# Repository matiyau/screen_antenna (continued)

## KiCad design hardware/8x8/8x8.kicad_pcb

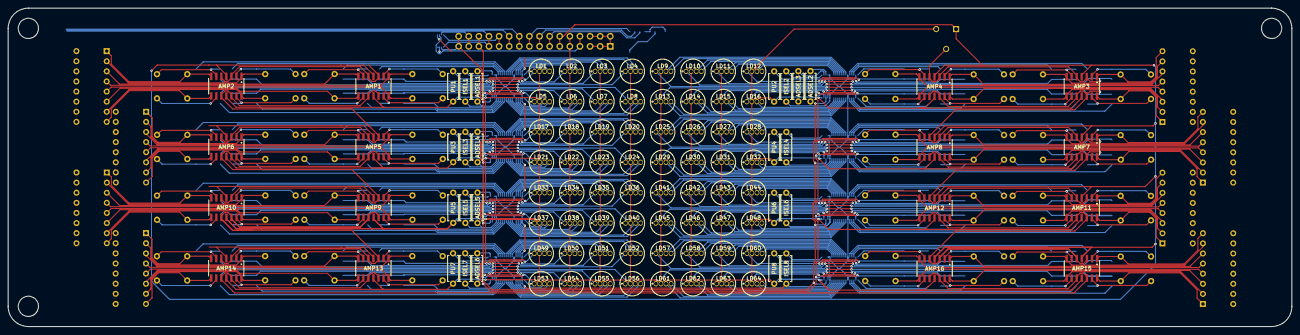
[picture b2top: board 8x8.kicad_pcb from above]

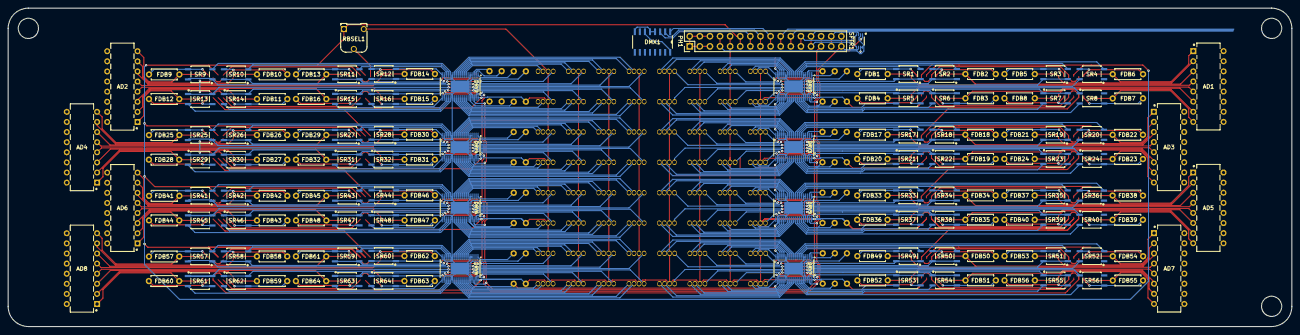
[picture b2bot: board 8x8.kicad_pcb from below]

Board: 2 copper layers, 322.6 x 80.0 mm, 250 parts (148 on the bottom side), 429 nets.

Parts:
AD1, AD2, AD3, AD4, AD5, AD6, AD7, AD8: MCP3008-I/P-DIP16; MCP3008-I&slash_P
ADSEL1, ADSEL2, ADSEL3, ADSEL4, ADSEL5, ADSEL6: 100K; footprints
AMP1, AMP2, AMP3, AMP4, AMP5, AMP6, AMP7, AMP8, AMP9, AMP10, AMP11, AMP12, AMP13, AMP14, AMP15, AMP16: MCP619-I/SL; footprints
DMX1: 74HC138D-Q100,118; footprints
DRV1, DRV2, DRV3, DRV4, DRV5, DRV6, DRV7, DRV8: PCA9956BTWY; SOP50P640X110-39N
FDB1, FDB2, FDB3, FDB4, FDB5, FDB6, FDB7, FDB8, FDB9, FDB10, FDB11, FDB12, FDB13, FDB14, FDB15, FDB16, FDB17, FDB18, FDB19, FDB20, FDB21, FDB22, FDB23, FDB24, FDB25, FDB26, FDB27, FDB28, FDB29, FDB30, FDB31, FDB32, FDB33, FDB34, FDB35, FDB36, FDB37, FDB38, FDB39, FDB40, FDB41, FDB42, FDB43, FDB44, FDB45, FDB46, FDB47, FDB48, FDB49, FDB50, FDB51, FDB52, FDB53, FDB54, FDB55, FDB56, FDB57, FDB58, FDB59, FDB60, FDB61, FDB62, FDB63, FDB64: 2M; footprints
ISEL1, ISEL2, ISEL3, ISEL4, ISEL5, ISEL6, ISEL7, ISEL8: 2K; footprints
LD1, LD2, LD3, LD4, LD5, LD6, LD7, LD8, LD9, LD10, LD11, LD12, LD13, LD14, LD15, LD16, LD17, LD18, LD19, LD20, LD21, LD22, LD23, LD24, LD25, LD26, LD27, LD28, LD29, LD30, LD31, LD32, LD33, LD34, LD35, LD36, LD37, LD38, LD39, LD40, LD41, LD42, LD43, LD44, LD45, LD46, LD47, LD48, LD49, LD50, LD51, LD52, LD53, LD54, LD55, LD56, LD57, LD58, LD59, LD60, LD61, LD62, LD63, LD64: WP154A4SEJ3VBDZGC/CA; WP154A4SEJ3VBDZGC&slash_CA
PH1: Conn_02x16_Odd_Even; PinHeader_2x16_P2.54mm_Vertical
PU1, PU2, PU3, PU4, PU5, PU6, PU7, PU8: 10K; footprints
RBSEL1: 100K; Potentiometer_Runtron_RM-065_Vertical
SFTR1: VSSOP8_SOT765-1_NEX; LSF0102DCH
SR1, SR2, SR3, SR4, SR5, SR6, SR7, SR8, SR9, SR10, SR11, SR12, SR13, SR14, SR15, SR16, SR17, SR18, SR19, SR20, SR21, SR22, SR23, SR24, SR25, SR26, SR27, SR28, SR29, SR30, SR31, SR32, SR33, SR34, SR35, SR36, SR37, SR38, SR39, SR40, SR41, SR42, SR43, SR44, SR45, SR46, SR47, SR48, SR49, SR50, SR51, SR52, SR53, SR54, SR55, SR56, SR57, SR58, SR59, SR60, SR61, SR62, SR63, SR64: TLP4176ATP_F; footprints

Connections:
+3V3: PH1.7, PH1.8, SFTR1.2 (REFA)
+5V: AD1.15 (VREF), AD1.16 (VDD), AD2.15 (VREF), AD2.16 (VDD), AD3.15 (VREF), AD3.16 (VDD), AD4.15 (VREF), AD4.16 (VDD), AD5.15 (VREF), AD5.16 (VDD), AD6.15 (VREF), AD6.16 (VDD), AD7.15 (VREF), AD7.16 (VDD), AD8.15 (VREF), AD8.16 (VDD), ADSEL3.2, ADSEL6.2, AMP1.11 (VSS), AMP2.11 (VSS), AMP3.11 (VSS), AMP4.11 (VSS), AMP5.11 (VSS), AMP6.11 (VSS), AMP7.11 (VSS), AMP8.11 (VSS), AMP9.11 (VSS), AMP10.11 (VSS), AMP11.11 (VSS), AMP12.11 (VSS), AMP13.11 (VSS), AMP14.11 (VSS), AMP15.11 (VSS), AMP16.11 (VSS), DMX1.6 (E3), DMX1.16 (VCC), DRV1.38 (VDD), DRV2.38 (VDD), DRV3.2 (AD0), DRV3.38 (VDD), DRV4.38 (VDD), DRV5.38 (VDD), DRV6.38 (VDD), DRV7.38 (VDD), DRV8.2 (AD0), DRV8.38 (VDD), LD1.2 (CA), LD2.2 (CA), LD3.2 (CA), LD4.2 (CA), LD5.2 (CA), LD6.2 (CA), LD7.2 (CA), LD8.2 (CA), LD9.2 (CA), LD10.2 (CA), LD11.2 (CA), LD12.2 (CA), LD13.2 (CA), LD14.2 (CA), LD15.2 (CA), LD16.2 (CA), LD17.2 (CA), LD18.2 (CA), LD19.2 (CA), LD20.2 (CA), LD21.2 (CA), LD22.2 (CA), LD23.2 (CA), LD24.2 (CA), LD25.2 (CA), LD26.2 (CA), LD27.2 (CA), LD28.2 (CA), LD29.2 (CA), LD30.2 (CA), LD31.2 (CA), LD32.2 (CA), LD33.2 (CA), LD34.2 (CA), LD35.2 (CA), LD36.2 (CA), LD37.2 (CA), LD38.2 (CA), LD39.2 (CA), LD40.2 (CA), LD41.2 (CA), LD42.2 (CA), LD43.2 (CA), LD44.2 (CA), LD45.2 (CA), LD46.2 (CA), LD47.2 (CA), LD48.2 (CA), LD49.2 (CA), LD50.2 (CA), LD51.2 (CA), LD52.2 (CA), LD53.2 (CA), LD54.2 (CA), LD55.2 (CA), LD56.2 (CA), LD57.2 (CA), LD58.2 (CA), LD59.2 (CA), LD60.2 (CA), LD61.2 (CA), LD62.2 (CA), LD63.2 (CA), LD64.2 (CA), PH1.9, PH1.10, PU1.1, PU2.1, PU3.1, PU4.1, PU5.1, PU6.1, PU7.1, PU8.1, RBSEL1.3, SFTR1.7 (REFB), SFTR1.8 (EN)
+9V: AMP1.4 (VDD), AMP2.4 (VDD), AMP3.4 (VDD), AMP4.4 (VDD), AMP5.4 (VDD), AMP6.4 (VDD), AMP7.4 (VDD), AMP8.4 (VDD), AMP9.4 (VDD), AMP10.4 (VDD), AMP11.4 (VDD), AMP12.4 (VDD), AMP13.4 (VDD), AMP14.4 (VDD), AMP15.4 (VDD), AMP16.4 (VDD), PH1.11, PH1.12, RBSEL1.1
/LED 4x2 Left 1/ LDRow_Amps1/Amp_IP_1: AMP1.2 (VINA-), FDB1.2, SR1.3 (Load)
/LED 4x2 Left 1/ LDRow_Amps1/Amp_IP_2: AMP1.6 (VINB-), FDB2.2, SR2.3 (Load)
/LED 4x2 Left 1/ LDRow_Amps1/Amp_IP_3: AMP1.9 (VINC-), FDB3.2, SR6.3 (Load)
/LED 4x2 Left 1/ LDRow_Amps1/Amp_IP_4: AMP1.13 (VIND-), FDB4.2, SR5.3 (Load)
/LED 4x2 Left 1/ LDRow_Amps1/Amp_IP_5: AMP2.2 (VINA-), FDB5.2, SR3.3 (Load)
/LED 4x2 Left 1/ LDRow_Amps1/Amp_IP_6: AMP2.6 (VINB-), FDB6.2, SR4.3 (Load)
/LED 4x2 Left 1/ LDRow_Amps1/Amp_IP_7: AMP2.9 (VINC-), FDB7.2, SR8.3 (Load)
/LED 4x2 Left 1/ LDRow_Amps1/Amp_IP_8: AMP2.13 (VIND-), FDB8.2, SR7.3 (Load)
/LED 4x2 Left 1/ LDRow_Amps1/Amp_OP_1: AD1.4 (CH3), AMP1.1 (VOUTA), FDB1.1
/LED 4x2 Left 1/ LDRow_Amps1/Amp_OP_2: AD1.3 (CH2), AMP1.7 (VOUTB), FDB2.1
/LED 4x2 Left 1/ LDRow_Amps1/Amp_OP_3: AD1.6 (CH5), AMP1.8 (VOUTC), FDB3.1
/LED 4x2 Left 1/ LDRow_Amps1/Amp_OP_4: AD1.5 (CH4), AMP1.14 (VOUTD), FDB4.1
/LED 4x2 Left 1/ LDRow_Amps1/Amp_OP_5: AD1.2 (CH1), AMP2.1 (VOUTA), FDB5.1
/LED 4x2 Left 1/ LDRow_Amps1/Amp_OP_6: AD1.1 (CH0), AMP2.7 (VOUTB), FDB6.1
/LED 4x2 Left 1/ LDRow_Amps1/Amp_OP_7: AD1.8 (CH7), AMP2.8 (VOUTC), FDB7.1
/LED 4x2 Left 1/ LDRow_Amps1/Amp_OP_8: AD1.7 (CH6), AMP2.14 (VOUTD), FDB8.1
/LED 4x2 Left 1/ADC_SHDN: AD1.10 (SHDN/~CS), DMX1.15 (~Y0)
/LED 4x2 Left 1/Drv_AD1: ADSEL1.1, DRV1.3 (AD1)
/LED 4x2 Left 1/LD1_B: DRV1.19 (LED11), LD1.3 (B)
/LED 4x2 Left 1/LD1_G: DRV1.17 (LED10), LD1.4 (G)
/LED 4x2 Left 1/LD1_R: LD1.1 (R), SR1.1 (+Ctr), SR1.4 (Load)
/LED 4x2 Left 1/LD2_B: DRV1.16 (LED9), LD2.3 (B)
/LED 4x2 Left 1/LD2_G: DRV1.15 (LED8), LD2.4 (G)
/LED 4x2 Left 1/LD2_R: LD2.1 (R), SR2.1 (+Ctr), SR2.4 (Load)
/LED 4x2 Left 1/LD3_B: DRV1.13 (LED7), LD3.3 (B)
/LED 4x2 Left 1/LD3_G: DRV1.12 (LED6), LD3.4 (G)
/LED 4x2 Left 1/LD3_R: LD3.1 (R), SR3.1 (+Ctr), SR3.4 (Load)
/LED 4x2 Left 1/LD4_B: DRV1.11 (LED5), LD4.3 (B)
/LED 4x2 Left 1/LD4_G: DRV1.10 (LED4), LD4.4 (G)
/LED 4x2 Left 1/LD4_R: LD4.1 (R), SR4.1 (+Ctr), SR4.4 (Load)
/LED 4x2 Left 1/LD5_B: DRV1.20 (LED12), LD5.3 (B)
/LED 4x2 Left 1/LD5_G: DRV1.22 (LED13), LD5.4 (G)
/LED 4x2 Left 1/LD5_R: LD5.1 (R), SR5.1 (+Ctr), SR5.4 (Load)
/LED 4x2 Left 1/LD6_B: DRV1.23 (LED14), LD6.3 (B)
/LED 4x2 Left 1/LD6_G: DRV1.24 (LED15), LD6.4 (G)
/LED 4x2 Left 1/LD6_R: LD6.1 (R), SR6.1 (+Ctr), SR6.4 (Load)
/LED 4x2 Left 1/LD7_B: DRV1.26 (LED16), LD7.3 (B)
/LED 4x2 Left 1/LD7_G: DRV1.27 (LED17), LD7.4 (G)
/LED 4x2 Left 1/LD7_R: LD7.1 (R), SR7.1 (+Ctr), SR7.4 (Load)
/LED 4x2 Left 1/LD8_B: DRV1.28 (LED18), LD8.3 (B)
/LED 4x2 Left 1/LD8_G: DRV1.29 (LED19), LD8.4 (G)
/LED 4x2 Left 1/LD8_R: LD8.1 (R), SR8.1 (+Ctr), SR8.4 (Load)
/LED 4x2 Left 1/SR1_R: DRV1.6 (LED0), SR1.2 (-Ctr)
/LED 4x2 Left 1/SR2_R: DRV1.7 (LED1), SR2.2 (-Ctr)
/LED 4x2 Left 1/SR3_R: DRV1.8 (LED2), SR3.2 (-Ctr)
/LED 4x2 Left 1/SR4_R: DRV1.9 (LED3), SR4.2 (-Ctr)
/LED 4x2 Left 1/SR5_R: DRV1.33 (LED23), SR5.2 (-Ctr)
/LED 4x2 Left 1/SR6_R: DRV1.32 (LED22), SR6.2 (-Ctr)
/LED 4x2 Left 1/SR7_R: DRV1.31 (LED21), SR7.2 (-Ctr)
/LED 4x2 Left 1/SR8_R: DRV1.30 (LED20), SR8.2 (-Ctr)
/LED 4x2 Left 2/ LDRow_Amps1/Amp_IP_1: AMP5.2 (VINA-), FDB17.2, SR17.3 (Load)
/LED 4x2 Left 2/ LDRow_Amps1/Amp_IP_2: AMP5.6 (VINB-), FDB18.2, SR18.3 (Load)
/LED 4x2 Left 2/ LDRow_Amps1/Amp_IP_3: AMP5.9 (VINC-), FDB19.2, SR22.3 (Load)
/LED 4x2 Left 2/ LDRow_Amps1/Amp_IP_4: AMP5.13 (VIND-), FDB20.2, SR21.3 (Load)
/LED 4x2 Left 2/ LDRow_Amps1/Amp_IP_5: AMP6.2 (VINA-), FDB21.2, SR19.3 (Load)
/LED 4x2 Left 2/ LDRow_Amps1/Amp_IP_6: AMP6.6 (VINB-), FDB22.2, SR20.3 (Load)
/LED 4x2 Left 2/ LDRow_Amps1/Amp_IP_7: AMP6.9 (VINC-), FDB23.2, SR24.3 (Load)
/LED 4x2 Left 2/ LDRow_Amps1/Amp_IP_8: AMP6.13 (VIND-), FDB24.2, SR23.3 (Load)
/LED 4x2 Left 2/ LDRow_Amps1/Amp_OP_1: AD3.4 (CH3), AMP5.1 (VOUTA), FDB17.1
/LED 4x2 Left 2/ LDRow_Amps1/Amp_OP_2: AD3.3 (CH2), AMP5.7 (VOUTB), FDB18.1
/LED 4x2 Left 2/ LDRow_Amps1/Amp_OP_3: AD3.6 (CH5), AMP5.8 (VOUTC), FDB19.1
/LED 4x2 Left 2/ LDRow_Amps1/Amp_OP_4: AD3.5 (CH4), AMP5.14 (VOUTD), FDB20.1
/LED 4x2 Left 2/ LDRow_Amps1/Amp_OP_5: AD3.2 (CH1), AMP6.1 (VOUTA), FDB21.1
/LED 4x2 Left 2/ LDRow_Amps1/Amp_OP_6: AD3.1 (CH0), AMP6.7 (VOUTB), FDB22.1
/LED 4x2 Left 2/ LDRow_Amps1/Amp_OP_7: AD3.8 (CH7), AMP6.8 (VOUTC), FDB23.1
/LED 4x2 Left 2/ LDRow_Amps1/Amp_OP_8: AD3.7 (CH6), AMP6.14 (VOUTD), FDB24.1
/LED 4x2 Left 2/ADC_SHDN: AD3.10 (SHDN/~CS), DMX1.13 (~Y2)
/LED 4x2 Left 2/Drv_AD1: ADSEL4.1, DRV3.3 (AD1)
/LED 4x2 Left 2/LD1_B: DRV3.19 (LED11), LD17.3 (B)
/LED 4x2 Left 2/LD1_G: DRV3.17 (LED10), LD17.4 (G)
/LED 4x2 Left 2/LD1_R: LD17.1 (R), SR17.1 (+Ctr), SR17.4 (Load)
/LED 4x2 Left 2/LD2_B: DRV3.16 (LED9), LD18.3 (B)
/LED 4x2 Left 2/LD2_G: DRV3.15 (LED8), LD18.4 (G)
/LED 4x2 Left 2/LD2_R: LD18.1 (R), SR18.1 (+Ctr), SR18.4 (Load)
/LED 4x2 Left 2/LD3_B: DRV3.13 (LED7), LD19.3 (B)
/LED 4x2 Left 2/LD3_G: DRV3.12 (LED6), LD19.4 (G)
/LED 4x2 Left 2/LD3_R: LD19.1 (R), SR19.1 (+Ctr), SR19.4 (Load)
/LED 4x2 Left 2/LD4_B: DRV3.11 (LED5), LD20.3 (B)
/LED 4x2 Left 2/LD4_G: DRV3.10 (LED4), LD20.4 (G)
/LED 4x2 Left 2/LD4_R: LD20.1 (R), SR20.1 (+Ctr), SR20.4 (Load)
/LED 4x2 Left 2/LD5_B: DRV3.20 (LED12), LD21.3 (B)
/LED 4x2 Left 2/LD5_G: DRV3.22 (LED13), LD21.4 (G)
/LED 4x2 Left 2/LD5_R: LD21.1 (R), SR21.1 (+Ctr), SR21.4 (Load)
/LED 4x2 Left 2/LD6_B: DRV3.23 (LED14), LD22.3 (B)
/LED 4x2 Left 2/LD6_G: DRV3.24 (LED15), LD22.4 (G)
/LED 4x2 Left 2/LD6_R: LD22.1 (R), SR22.1 (+Ctr), SR22.4 (Load)
/LED 4x2 Left 2/LD7_B: DRV3.26 (LED16), LD23.3 (B)
/LED 4x2 Left 2/LD7_G: DRV3.27 (LED17), LD23.4 (G)
/LED 4x2 Left 2/LD7_R: LD23.1 (R), SR23.1 (+Ctr), SR23.4 (Load)
/LED 4x2 Left 2/LD8_B: DRV3.28 (LED18), LD24.3 (B)
/LED 4x2 Left 2/LD8_G: DRV3.29 (LED19), LD24.4 (G)
/LED 4x2 Left 2/LD8_R: LD24.1 (R), SR24.1 (+Ctr), SR24.4 (Load)
/LED 4x2 Left 2/SR1_R: DRV3.6 (LED0), SR17.2 (-Ctr)
/LED 4x2 Left 2/SR2_R: DRV3.7 (LED1), SR18.2 (-Ctr)
/LED 4x2 Left 2/SR3_R: DRV3.8 (LED2), SR19.2 (-Ctr)
/LED 4x2 Left 2/SR4_R: DRV3.9 (LED3), SR20.2 (-Ctr)
/LED 4x2 Left 2/SR5_R: DRV3.33 (LED23), SR21.2 (-Ctr)
/LED 4x2 Left 2/SR6_R: DRV3.32 (LED22), SR22.2 (-Ctr)
/LED 4x2 Left 2/SR7_R: DRV3.31 (LED21), SR23.2 (-Ctr)
/LED 4x2 Left 2/SR8_R: DRV3.30 (LED20), SR24.2 (-Ctr)
/LED 4x2 Left 3/ LDRow_Amps1/Amp_IP_1: AMP9.2 (VINA-), FDB33.2, SR33.3 (Load)
/LED 4x2 Left 3/ LDRow_Amps1/Amp_IP_2: AMP9.6 (VINB-), FDB34.2, SR34.3 (Load)
/LED 4x2 Left 3/ LDRow_Amps1/Amp_IP_3: AMP9.9 (VINC-), FDB35.2, SR38.3 (Load)
/LED 4x2 Left 3/ LDRow_Amps1/Amp_IP_4: AMP9.13 (VIND-), FDB36.2, SR37.3 (Load)
/LED 4x2 Left 3/ LDRow_Amps1/Amp_IP_5: AMP10.2 (VINA-), FDB37.2, SR35.3 (Load)
/LED 4x2 Left 3/ LDRow_Amps1/Amp_IP_6: AMP10.6 (VINB-), FDB38.2, SR36.3 (Load)
/LED 4x2 Left 3/ LDRow_Amps1/Amp_IP_7: AMP10.9 (VINC-), FDB39.2, SR40.3 (Load)
/LED 4x2 Left 3/ LDRow_Amps1/Amp_IP_8: AMP10.13 (VIND-), FDB40.2, SR39.3 (Load)
/LED 4x2 Left 3/ LDRow_Amps1/Amp_OP_1: AD5.4 (CH3), AMP9.1 (VOUTA), FDB33.1
/LED 4x2 Left 3/ LDRow_Amps1/Amp_OP_2: AD5.3 (CH2), AMP9.7 (VOUTB), FDB34.1
/LED 4x2 Left 3/ LDRow_Amps1/Amp_OP_3: AD5.6 (CH5), AMP9.8 (VOUTC), FDB35.1
/LED 4x2 Left 3/ LDRow_Amps1/Amp_OP_4: AD5.5 (CH4), AMP9.14 (VOUTD), FDB36.1
/LED 4x2 Left 3/ LDRow_Amps1/Amp_OP_5: AD5.2 (CH1), AMP10.1 (VOUTA), FDB37.1
/LED 4x2 Left 3/ LDRow_Amps1/Amp_OP_6: AD5.1 (CH0), AMP10.7 (VOUTB), FDB38.1
/LED 4x2 Left 3/ LDRow_Amps1/Amp_OP_7: AD5.8 (CH7), AMP10.8 (VOUTC), FDB39.1
/LED 4x2 Left 3/ LDRow_Amps1/Amp_OP_8: AD5.7 (CH6), AMP10.14 (VOUTD), FDB40.1
/LED 4x2 Left 3/ADC_SHDN: AD5.10 (SHDN/~CS), DMX1.14 (~Y1)
/LED 4x2 Left 3/Drv_AD0: ADSEL5.1, DRV5.2 (AD0)
/LED 4x2 Left 3/LD1_B: DRV5.19 (LED11), LD33.3 (B)
/LED 4x2 Left 3/LD1_G: DRV5.17 (LED10), LD33.4 (G)
/LED 4x2 Left 3/LD1_R: LD33.1 (R), SR33.1 (+Ctr), SR33.4 (Load)
/LED 4x2 Left 3/LD2_B: DRV5.16 (LED9), LD34.3 (B)
/LED 4x2 Left 3/LD2_G: DRV5.15 (LED8), LD34.4 (G)
/LED 4x2 Left 3/LD2_R: LD34.1 (R), SR34.1 (+Ctr), SR34.4 (Load)
/LED 4x2 Left 3/LD3_B: DRV5.13 (LED7), LD35.3 (B)
/LED 4x2 Left 3/LD3_G: DRV5.12 (LED6), LD35.4 (G)
/LED 4x2 Left 3/LD3_R: LD35.1 (R), SR35.1 (+Ctr), SR35.4 (Load)
/LED 4x2 Left 3/LD4_B: DRV5.11 (LED5), LD36.3 (B)
/LED 4x2 Left 3/LD4_G: DRV5.10 (LED4), LD36.4 (G)
/LED 4x2 Left 3/LD4_R: LD36.1 (R), SR36.1 (+Ctr), SR36.4 (Load)
/LED 4x2 Left 3/LD5_B: DRV5.20 (LED12), LD37.3 (B)
/LED 4x2 Left 3/LD5_G: DRV5.22 (LED13), LD37.4 (G)
/LED 4x2 Left 3/LD5_R: LD37.1 (R), SR37.1 (+Ctr), SR37.4 (Load)
/LED 4x2 Left 3/LD6_B: DRV5.23 (LED14), LD38.3 (B)
/LED 4x2 Left 3/LD6_G: DRV5.24 (LED15), LD38.4 (G)
/LED 4x2 Left 3/LD6_R: LD38.1 (R), SR38.1 (+Ctr), SR38.4 (Load)
/LED 4x2 Left 3/LD7_B: DRV5.26 (LED16), LD39.3 (B)
/LED 4x2 Left 3/LD7_G: DRV5.27 (LED17), LD39.4 (G)
/LED 4x2 Left 3/LD7_R: LD39.1 (R), SR39.1 (+Ctr), SR39.4 (Load)
/LED 4x2 Left 3/LD8_B: DRV5.28 (LED18), LD40.3 (B)
/LED 4x2 Left 3/LD8_G: DRV5.29 (LED19), LD40.4 (G)
/LED 4x2 Left 3/LD8_R: LD40.1 (R), SR40.1 (+Ctr), SR40.4 (Load)
/LED 4x2 Left 3/SR1_R: DRV5.6 (LED0), SR33.2 (-Ctr)
/LED 4x2 Left 3/SR2_R: DRV5.7 (LED1), SR34.2 (-Ctr)
/LED 4x2 Left 3/SR3_R: DRV5.8 (LED2), SR35.2 (-Ctr)
/LED 4x2 Left 3/SR4_R: DRV5.9 (LED3), SR36.2 (-Ctr)
/LED 4x2 Left 3/SR5_R: DRV5.33 (LED23), SR37.2 (-Ctr)
/LED 4x2 Left 3/SR6_R: DRV5.32 (LED22), SR38.2 (-Ctr)
/LED 4x2 Left 3/SR7_R: DRV5.31 (LED21), SR39.2 (-Ctr)
/LED 4x2 Left 3/SR8_R: DRV5.30 (LED20), SR40.2 (-Ctr)
/LED 4x2 Left 4/ LDRow_Amps1/Amp_IP_1: AMP13.2 (VINA-), FDB49.2, SR49.3 (Load)
/LED 4x2 Left 4/ LDRow_Amps1/Amp_IP_2: AMP13.6 (VINB-), FDB50.2, SR50.3 (Load)
/LED 4x2 Left 4/ LDRow_Amps1/Amp_IP_3: AMP13.9 (VINC-), FDB51.2, SR54.3 (Load)
/LED 4x2 Left 4/ LDRow_Amps1/Amp_IP_4: AMP13.13 (VIND-), FDB52.2, SR53.3 (Load)
/LED 4x2 Left 4/ LDRow_Amps1/Amp_IP_5: AMP14.2 (VINA-), FDB53.2, SR51.3 (Load)
/LED 4x2 Left 4/ LDRow_Amps1/Amp_IP_6: AMP14.6 (VINB-), FDB54.2, SR52.3 (Load)
/LED 4x2 Left 4/ LDRow_Amps1/Amp_IP_7: AMP14.9 (VINC-), FDB55.2, SR56.3 (Load)
/LED 4x2 Left 4/ LDRow_Amps1/Amp_IP_8: AMP14.13 (VIND-), FDB56.2, SR55.3 (Load)
/LED 4x2 Left 4/ LDRow_Amps1/Amp_OP_1: AD7.4 (CH3), AMP13.1 (VOUTA), FDB49.1
/LED 4x2 Left 4/ LDRow_Amps1/Amp_OP_2: AD7.3 (CH2), AMP13.7 (VOUTB), FDB50.1
/LED 4x2 Left 4/ LDRow_Amps1/Amp_OP_3: AD7.6 (CH5), AMP13.8 (VOUTC), FDB51.1
/LED 4x2 Left 4/ LDRow_Amps1/Amp_OP_4: AD7.5 (CH4), AMP13.14 (VOUTD), FDB52.1
/LED 4x2 Left 4/ LDRow_Amps1/Amp_OP_5: AD7.2 (CH1), AMP14.1 (VOUTA), FDB53.1
/LED 4x2 Left 4/ LDRow_Amps1/Amp_OP_6: AD7.1 (CH0), AMP14.7 (VOUTB), FDB54.1
/LED 4x2 Left 4/ LDRow_Amps1/Amp_OP_7: AD7.8 (CH7), AMP14.8 (VOUTC), FDB55.1
/LED 4x2 Left 4/ LDRow_Amps1/Amp_OP_8: AD7.7 (CH6), AMP14.14 (VOUTD), FDB56.1
/LED 4x2 Left 4/ADC_SHDN: AD7.10 (SHDN/~CS), DMX1.12 (~Y3)
/LED 4x2 Left 4/Drv_AD0: ADSEL6.1, DRV7.2 (AD0)
/LED 4x2 Left 4/LD1_B: DRV7.19 (LED11), LD49.3 (B)
/LED 4x2 Left 4/LD1_G: DRV7.17 (LED10), LD49.4 (G)
/LED 4x2 Left 4/LD1_R: LD49.1 (R), SR49.1 (+Ctr), SR49.4 (Load)
/LED 4x2 Left 4/LD2_B: DRV7.16 (LED9), LD50.3 (B)
/LED 4x2 Left 4/LD2_G: DRV7.15 (LED8), LD50.4 (G)
/LED 4x2 Left 4/LD2_R: LD50.1 (R), SR50.1 (+Ctr), SR50.4 (Load)
/LED 4x2 Left 4/LD3_B: DRV7.13 (LED7), LD51.3 (B)
/LED 4x2 Left 4/LD3_G: DRV7.12 (LED6), LD51.4 (G)
/LED 4x2 Left 4/LD3_R: LD51.1 (R), SR51.1 (+Ctr), SR51.4 (Load)
/LED 4x2 Left 4/LD4_B: DRV7.11 (LED5), LD52.3 (B)
/LED 4x2 Left 4/LD4_G: DRV7.10 (LED4), LD52.4 (G)
/LED 4x2 Left 4/LD4_R: LD52.1 (R), SR52.1 (+Ctr), SR52.4 (Load)
/LED 4x2 Left 4/LD5_B: DRV7.20 (LED12), LD53.3 (B)
/LED 4x2 Left 4/LD5_G: DRV7.22 (LED13), LD53.4 (G)
/LED 4x2 Left 4/LD5_R: LD53.1 (R), SR53.1 (+Ctr), SR53.4 (Load)
/LED 4x2 Left 4/LD6_B: DRV7.23 (LED14), LD54.3 (B)
/LED 4x2 Left 4/LD6_G: DRV7.24 (LED15), LD54.4 (G)
/LED 4x2 Left 4/LD6_R: LD54.1 (R), SR54.1 (+Ctr), SR54.4 (Load)
/LED 4x2 Left 4/LD7_B: DRV7.26 (LED16), LD55.3 (B)
/LED 4x2 Left 4/LD7_G: DRV7.27 (LED17), LD55.4 (G)
/LED 4x2 Left 4/LD7_R: LD55.1 (R), SR55.1 (+Ctr), SR55.4 (Load)
/LED 4x2 Left 4/LD8_B: DRV7.28 (LED18), LD56.3 (B)
/LED 4x2 Left 4/LD8_G: DRV7.29 (LED19), LD56.4 (G)
/LED 4x2 Left 4/LD8_R: LD56.1 (R), SR56.1 (+Ctr), SR56.4 (Load)
/LED 4x2 Left 4/SR1_R: DRV7.6 (LED0), SR49.2 (-Ctr)
/LED 4x2 Left 4/SR2_R: DRV7.7 (LED1), SR50.2 (-Ctr)
/LED 4x2 Left 4/SR3_R: DRV7.8 (LED2), SR51.2 (-Ctr)
/LED 4x2 Left 4/SR4_R: DRV7.9 (LED3), SR52.2 (-Ctr)
/LED 4x2 Left 4/SR5_R: DRV7.33 (LED23), SR53.2 (-Ctr)
/LED 4x2 Left 4/SR6_R: DRV7.32 (LED22), SR54.2 (-Ctr)
/LED 4x2 Left 4/SR7_R: DRV7.31 (LED21), SR55.2 (-Ctr)
/LED 4x2 Left 4/SR8_R: DRV7.30 (LED20), SR56.2 (-Ctr)
/LED 4x2 Right 1/ LDRow_Amps/Amp_IP_1: AMP3.2 (VINA-), FDB9.2, SR9.3 (Load)
/LED 4x2 Right 1/ LDRow_Amps/Amp_IP_2: AMP3.6 (VINB-), FDB10.2, SR10.3 (Load)
/LED 4x2 Right 1/ LDRow_Amps/Amp_IP_3: AMP3.9 (VINC-), FDB11.2, SR14.3 (Load)
/LED 4x2 Right 1/ LDRow_Amps/Amp_IP_4: AMP3.13 (VIND-), FDB12.2, SR13.3 (Load)
/LED 4x2 Right 1/ LDRow_Amps/Amp_IP_5: AMP4.2 (VINA-), FDB13.2, SR11.3 (Load)
/LED 4x2 Right 1/ LDRow_Amps/Amp_IP_6: AMP4.6 (VINB-), FDB14.2, SR12.3 (Load)
/LED 4x2 Right 1/ LDRow_Amps/Amp_IP_7: AMP4.9 (VINC-), FDB15.2, SR16.3 (Load)
/LED 4x2 Right 1/ LDRow_Amps/Amp_IP_8: AMP4.13 (VIND-), FDB16.2, SR15.3 (Load)
/LED 4x2 Right 1/ LDRow_Amps/Amp_OP_1: AD2.8 (CH7), AMP3.1 (VOUTA), FDB9.1
/LED 4x2 Right 1/ LDRow_Amps/Amp_OP_2: AD2.7 (CH6), AMP3.7 (VOUTB), FDB10.1
/LED 4x2 Right 1/ LDRow_Amps/Amp_OP_3: AD2.2 (CH1), AMP3.8 (VOUTC), FDB11.1
/LED 4x2 Right 1/ LDRow_Amps/Amp_OP_4: AD2.1 (CH0), AMP3.14 (VOUTD), FDB12.1
/LED 4x2 Right 1/ LDRow_Amps/Amp_OP_5: AD2.6 (CH5), AMP4.1 (VOUTA), FDB13.1
/LED 4x2 Right 1/ LDRow_Amps/Amp_OP_6: AD2.5 (CH4), AMP4.7 (VOUTB), FDB14.1
/LED 4x2 Right 1/ LDRow_Amps/Amp_OP_7: AD2.4 (CH3), AMP4.8 (VOUTC), FDB15.1
/LED 4x2 Right 1/ LDRow_Amps/Amp_OP_8: AD2.3 (CH2), AMP4.14 (VOUTD), FDB16.1
/LED 4x2 Right 1/ADC_SHDN: AD2.10 (SHDN/~CS), DMX1.10 (~Y5)
/LED 4x2 Right 1/Drv_AD0: ADSEL3.1, DRV2.2 (AD0)
/LED 4x2 Right 1/Drv_AD1: ADSEL2.1, DRV2.3 (AD1)
/LED 4x2 Right 1/LD1_B: DRV2.13 (LED7), LD9.3 (B)
/LED 4x2 Right 1/LD1_G: DRV2.12 (LED6), LD9.4 (G)
/LED 4x2 Right 1/LD1_R: LD9.1 (R), SR9.1 (+Ctr), SR9.4 (Load)
/LED 4x2 Right 1/LD2_B: DRV2.11 (LED5), LD10.3 (B)
/LED 4x2 Right 1/LD2_G: DRV2.10 (LED4), LD10.4 (G)
/LED 4x2 Right 1/LD2_R: LD10.1 (R), SR10.1 (+Ctr), SR10.4 (Load)
/LED 4x2 Right 1/LD3_B: DRV2.9 (LED3), LD11.3 (B)
/LED 4x2 Right 1/LD3_G: DRV2.8 (LED2), LD11.4 (G)
/LED 4x2 Right 1/LD3_R: LD11.1 (R), SR11.1 (+Ctr), SR11.4 (Load)
/LED 4x2 Right 1/LD4_B: DRV2.7 (LED1), LD12.3 (B)
/LED 4x2 Right 1/LD4_G: DRV2.6 (LED0), LD12.4 (G)
/LED 4x2 Right 1/LD4_R: LD12.1 (R), SR12.1 (+Ctr), SR12.4 (Load)
/LED 4x2 Right 1/LD5_B: DRV2.26 (LED16), LD13.3 (B)
/LED 4x2 Right 1/LD5_G: DRV2.27 (LED17), LD13.4 (G)
/LED 4x2 Right 1/LD5_R: LD13.1 (R), SR13.1 (+Ctr), SR13.4 (Load)
/LED 4x2 Right 1/LD6_B: DRV2.28 (LED18), LD14.3 (B)
/LED 4x2 Right 1/LD6_G: DRV2.29 (LED19), LD14.4 (G)
/LED 4x2 Right 1/LD6_R: LD14.1 (R), SR14.1 (+Ctr), SR14.4 (Load)
/LED 4x2 Right 1/LD7_B: DRV2.30 (LED20), LD15.3 (B)
/LED 4x2 Right 1/LD7_G: DRV2.31 (LED21), LD15.4 (G)
/LED 4x2 Right 1/LD7_R: LD15.1 (R), SR15.1 (+Ctr), SR15.4 (Load)
/LED 4x2 Right 1/LD8_B: DRV2.32 (LED22), LD16.3 (B)
/LED 4x2 Right 1/LD8_G: DRV2.33 (LED23), LD16.4 (G)
/LED 4x2 Right 1/LD8_R: LD16.1 (R), SR16.1 (+Ctr), SR16.4 (Load)
/LED 4x2 Right 1/SR1_R: DRV2.15 (LED8), SR9.2 (-Ctr)
/LED 4x2 Right 1/SR2_R: DRV2.16 (LED9), SR10.2 (-Ctr)
/LED 4x2 Right 1/SR3_R: DRV2.17 (LED10), SR11.2 (-Ctr)
/LED 4x2 Right 1/SR4_R: DRV2.19 (LED11), SR12.2 (-Ctr)
/LED 4x2 Right 1/SR5_R: DRV2.24 (LED15), SR13.2 (-Ctr)
/LED 4x2 Right 1/SR6_R: DRV2.23 (LED14), SR14.2 (-Ctr)
/LED 4x2 Right 1/SR7_R: DRV2.22 (LED13), SR15.2 (-Ctr)
/LED 4x2 Right 1/SR8_R: DRV2.20 (LED12), SR16.2 (-Ctr)
/LED 4x2 Right 2/ LDRow_Amps/Amp_IP_1: AMP7.2 (VINA-), FDB25.2, SR25.3 (Load)
/LED 4x2 Right 2/ LDRow_Amps/Amp_IP_2: AMP7.6 (VINB-), FDB26.2, SR26.3 (Load)
/LED 4x2 Right 2/ LDRow_Amps/Amp_IP_3: AMP7.9 (VINC-), FDB27.2, SR30.3 (Load)
/LED 4x2 Right 2/ LDRow_Amps/Amp_IP_4: AMP7.13 (VIND-), FDB28.2, SR29.3 (Load)
/LED 4x2 Right 2/ LDRow_Amps/Amp_IP_5: AMP8.2 (VINA-), FDB29.2, SR27.3 (Load)
/LED 4x2 Right 2/ LDRow_Amps/Amp_IP_6: AMP8.6 (VINB-), FDB30.2, SR28.3 (Load)
/LED 4x2 Right 2/ LDRow_Amps/Amp_IP_7: AMP8.9 (VINC-), FDB31.2, SR32.3 (Load)
/LED 4x2 Right 2/ LDRow_Amps/Amp_IP_8: AMP8.13 (VIND-), FDB32.2, SR31.3 (Load)
/LED 4x2 Right 2/ LDRow_Amps/Amp_OP_1: AD4.8 (CH7), AMP7.1 (VOUTA), FDB25.1
/LED 4x2 Right 2/ LDRow_Amps/Amp_OP_2: AD4.7 (CH6), AMP7.7 (VOUTB), FDB26.1
/LED 4x2 Right 2/ LDRow_Amps/Amp_OP_3: AD4.2 (CH1), AMP7.8 (VOUTC), FDB27.1
/LED 4x2 Right 2/ LDRow_Amps/Amp_OP_4: AD4.1 (CH0), AMP7.14 (VOUTD), FDB28.1
/LED 4x2 Right 2/ LDRow_Amps/Amp_OP_5: AD4.6 (CH5), AMP8.1 (VOUTA), FDB29.1
/LED 4x2 Right 2/ LDRow_Amps/Amp_OP_6: AD4.5 (CH4), AMP8.7 (VOUTB), FDB30.1
/LED 4x2 Right 2/ LDRow_Amps/Amp_OP_7: AD4.4 (CH3), AMP8.8 (VOUTC), FDB31.1
/LED 4x2 Right 2/ LDRow_Amps/Amp_OP_8: AD4.3 (CH2), AMP8.14 (VOUTD), FDB32.1
/LED 4x2 Right 2/ADC_SHDN: AD4.10 (SHDN/~CS), DMX1.7 (~Y7)
/LED 4x2 Right 2/LD1_B: DRV4.13 (LED7), LD25.3 (B)
/LED 4x2 Right 2/LD1_G: DRV4.12 (LED6), LD25.4 (G)
/LED 4x2 Right 2/LD1_R: LD25.1 (R), SR25.1 (+Ctr), SR25.4 (Load)
/LED 4x2 Right 2/LD2_B: DRV4.11 (LED5), LD26.3 (B)
/LED 4x2 Right 2/LD2_G: DRV4.10 (LED4), LD26.4 (G)
/LED 4x2 Right 2/LD2_R: LD26.1 (R), SR26.1 (+Ctr), SR26.4 (Load)
/LED 4x2 Right 2/LD3_B: DRV4.9 (LED3), LD27.3 (B)
/LED 4x2 Right 2/LD3_G: DRV4.8 (LED2), LD27.4 (G)
/LED 4x2 Right 2/LD3_R: LD27.1 (R), SR27.1 (+Ctr), SR27.4 (Load)
/LED 4x2 Right 2/LD4_B: DRV4.7 (LED1), LD28.3 (B)
/LED 4x2 Right 2/LD4_G: DRV4.6 (LED0), LD28.4 (G)
/LED 4x2 Right 2/LD4_R: LD28.1 (R), SR28.1 (+Ctr), SR28.4 (Load)
/LED 4x2 Right 2/LD5_B: DRV4.26 (LED16), LD29.3 (B)
/LED 4x2 Right 2/LD5_G: DRV4.27 (LED17), LD29.4 (G)
/LED 4x2 Right 2/LD5_R: LD29.1 (R), SR29.1 (+Ctr), SR29.4 (Load)
/LED 4x2 Right 2/LD6_B: DRV4.28 (LED18), LD30.3 (B)
/LED 4x2 Right 2/LD6_G: DRV4.29 (LED19), LD30.4 (G)
/LED 4x2 Right 2/LD6_R: LD30.1 (R), SR30.1 (+Ctr), SR30.4 (Load)
/LED 4x2 Right 2/LD7_B: DRV4.30 (LED20), LD31.3 (B)
/LED 4x2 Right 2/LD7_G: DRV4.31 (LED21), LD31.4 (G)
/LED 4x2 Right 2/LD7_R: LD31.1 (R), SR31.1 (+Ctr), SR31.4 (Load)
/LED 4x2 Right 2/LD8_B: DRV4.32 (LED22), LD32.3 (B)
/LED 4x2 Right 2/LD8_G: DRV4.33 (LED23), LD32.4 (G)
/LED 4x2 Right 2/LD8_R: LD32.1 (R), SR32.1 (+Ctr), SR32.4 (Load)
/LED 4x2 Right 2/SR1_R: DRV4.15 (LED8), SR25.2 (-Ctr)
/LED 4x2 Right 2/SR2_R: DRV4.16 (LED9), SR26.2 (-Ctr)
/LED 4x2 Right 2/SR3_R: DRV4.17 (LED10), SR27.2 (-Ctr)
/LED 4x2 Right 2/SR4_R: DRV4.19 (LED11), SR28.2 (-Ctr)
/LED 4x2 Right 2/SR5_R: DRV4.24 (LED15), SR29.2 (-Ctr)
/LED 4x2 Right 2/SR6_R: DRV4.23 (LED14), SR30.2 (-Ctr)
/LED 4x2 Right 2/SR7_R: DRV4.22 (LED13), SR31.2 (-Ctr)
/LED 4x2 Right 2/SR8_R: DRV4.20 (LED12), SR32.2 (-Ctr)
/LED 4x2 Right 3/ LDRow_Amps/Amp_IP_1: AMP11.2 (VINA-), FDB41.2, SR41.3 (Load)
/LED 4x2 Right 3/ LDRow_Amps/Amp_IP_2: AMP11.6 (VINB-), FDB42.2, SR42.3 (Load)
/LED 4x2 Right 3/ LDRow_Amps/Amp_IP_3: AMP11.9 (VINC-), FDB43.2, SR46.3 (Load)
/LED 4x2 Right 3/ LDRow_Amps/Amp_IP_4: AMP11.13 (VIND-), FDB44.2, SR45.3 (Load)
/LED 4x2 Right 3/ LDRow_Amps/Amp_IP_5: AMP12.2 (VINA-), FDB45.2, SR43.3 (Load)
/LED 4x2 Right 3/ LDRow_Amps/Amp_IP_6: AMP12.6 (VINB-), FDB46.2, SR44.3 (Load)
/LED 4x2 Right 3/ LDRow_Amps/Amp_IP_7: AMP12.9 (VINC-), FDB47.2, SR48.3 (Load)
/LED 4x2 Right 3/ LDRow_Amps/Amp_IP_8: AMP12.13 (VIND-), FDB48.2, SR47.3 (Load)
/LED 4x2 Right 3/ LDRow_Amps/Amp_OP_1: AD6.8 (CH7), AMP11.1 (VOUTA), FDB41.1
/LED 4x2 Right 3/ LDRow_Amps/Amp_OP_2: AD6.7 (CH6), AMP11.7 (VOUTB), FDB42.1
/LED 4x2 Right 3/ LDRow_Amps/Amp_OP_3: AD6.2 (CH1), AMP11.8 (VOUTC), FDB43.1
/LED 4x2 Right 3/ LDRow_Amps/Amp_OP_4: AD6.1 (CH0), AMP11.14 (VOUTD), FDB44.1
/LED 4x2 Right 3/ LDRow_Amps/Amp_OP_5: AD6.6 (CH5), AMP12.1 (VOUTA), FDB45.1
/LED 4x2 Right 3/ LDRow_Amps/Amp_OP_6: AD6.5 (CH4), AMP12.7 (VOUTB), FDB46.1
/LED 4x2 Right 3/ LDRow_Amps/Amp_OP_7: AD6.4 (CH3), AMP12.8 (VOUTC), FDB47.1
/LED 4x2 Right 3/ LDRow_Amps/Amp_OP_8: AD6.3 (CH2), AMP12.14 (VOUTD), FDB48.1
/LED 4x2 Right 3/ADC_SHDN: AD6.10 (SHDN/~CS), DMX1.11 (~Y4)
/LED 4x2 Right 3/LD1_B: DRV6.13 (LED7), LD41.3 (B)
/LED 4x2 Right 3/LD1_G: DRV6.12 (LED6), LD41.4 (G)
/LED 4x2 Right 3/LD1_R: LD41.1 (R), SR41.1 (+Ctr), SR41.4 (Load)
/LED 4x2 Right 3/LD2_B: DRV6.11 (LED5), LD42.3 (B)
/LED 4x2 Right 3/LD2_G: DRV6.10 (LED4), LD42.4 (G)
/LED 4x2 Right 3/LD2_R: LD42.1 (R), SR42.1 (+Ctr), SR42.4 (Load)
/LED 4x2 Right 3/LD3_B: DRV6.9 (LED3), LD43.3 (B)
/LED 4x2 Right 3/LD3_G: DRV6.8 (LED2), LD43.4 (G)
/LED 4x2 Right 3/LD3_R: LD43.1 (R), SR43.1 (+Ctr), SR43.4 (Load)
/LED 4x2 Right 3/LD4_B: DRV6.7 (LED1), LD44.3 (B)
/LED 4x2 Right 3/LD4_G: DRV6.6 (LED0), LD44.4 (G)
/LED 4x2 Right 3/LD4_R: LD44.1 (R), SR44.1 (+Ctr), SR44.4 (Load)
/LED 4x2 Right 3/LD5_B: DRV6.26 (LED16), LD45.3 (B)
/LED 4x2 Right 3/LD5_G: DRV6.27 (LED17), LD45.4 (G)
/LED 4x2 Right 3/LD5_R: LD45.1 (R), SR45.1 (+Ctr), SR45.4 (Load)
/LED 4x2 Right 3/LD6_B: DRV6.28 (LED18), LD46.3 (B)
/LED 4x2 Right 3/LD6_G: DRV6.29 (LED19), LD46.4 (G)
/LED 4x2 Right 3/LD6_R: LD46.1 (R), SR46.1 (+Ctr), SR46.4 (Load)
/LED 4x2 Right 3/LD7_B: DRV6.30 (LED20), LD47.3 (B)
/LED 4x2 Right 3/LD7_G: DRV6.31 (LED21), LD47.4 (G)
/LED 4x2 Right 3/LD7_R: LD47.1 (R), SR47.1 (+Ctr), SR47.4 (Load)
/LED 4x2 Right 3/LD8_B: DRV6.32 (LED22), LD48.3 (B)
/LED 4x2 Right 3/LD8_G: DRV6.33 (LED23), LD48.4 (G)
/LED 4x2 Right 3/LD8_R: LD48.1 (R), SR48.1 (+Ctr), SR48.4 (Load)
/LED 4x2 Right 3/SR1_R: DRV6.15 (LED8), SR41.2 (-Ctr)
/LED 4x2 Right 3/SR2_R: DRV6.16 (LED9), SR42.2 (-Ctr)
/LED 4x2 Right 3/SR3_R: DRV6.17 (LED10), SR43.2 (-Ctr)
/LED 4x2 Right 3/SR4_R: DRV6.19 (LED11), SR44.2 (-Ctr)
/LED 4x2 Right 3/SR5_R: DRV6.24 (LED15), SR45.2 (-Ctr)
/LED 4x2 Right 3/SR6_R: DRV6.23 (LED14), SR46.2 (-Ctr)
/LED 4x2 Right 3/SR7_R: DRV6.22 (LED13), SR47.2 (-Ctr)
/LED 4x2 Right 3/SR8_R: DRV6.20 (LED12), SR48.2 (-Ctr)
/LED 4x2 Right 4/ LDRow_Amps/Amp_IP_1: AMP15.2 (VINA-), FDB57.2, SR57.3 (Load)
/LED 4x2 Right 4/ LDRow_Amps/Amp_IP_2: AMP15.6 (VINB-), FDB58.2, SR58.3 (Load)
/LED 4x2 Right 4/ LDRow_Amps/Amp_IP_3: AMP15.9 (VINC-), FDB59.2, SR62.3 (Load)
/LED 4x2 Right 4/ LDRow_Amps/Amp_IP_4: AMP15.13 (VIND-), FDB60.2, SR61.3 (Load)
/LED 4x2 Right 4/ LDRow_Amps/Amp_IP_5: AMP16.2 (VINA-), FDB61.2, SR59.3 (Load)
/LED 4x2 Right 4/ LDRow_Amps/Amp_IP_6: AMP16.6 (VINB-), FDB62.2, SR60.3 (Load)
/LED 4x2 Right 4/ LDRow_Amps/Amp_IP_7: AMP16.9 (VINC-), FDB63.2, SR64.3 (Load)
/LED 4x2 Right 4/ LDRow_Amps/Amp_IP_8: AMP16.13 (VIND-), FDB64.2, SR63.3 (Load)
/LED 4x2 Right 4/ LDRow_Amps/Amp_OP_1: AD8.8 (CH7), AMP15.1 (VOUTA), FDB57.1
/LED 4x2 Right 4/ LDRow_Amps/Amp_OP_2: AD8.7 (CH6), AMP15.7 (VOUTB), FDB58.1
/LED 4x2 Right 4/ LDRow_Amps/Amp_OP_3: AD8.2 (CH1), AMP15.8 (VOUTC), FDB59.1
/LED 4x2 Right 4/ LDRow_Amps/Amp_OP_4: AD8.1 (CH0), AMP15.14 (VOUTD), FDB60.1
/LED 4x2 Right 4/ LDRow_Amps/Amp_OP_5: AD8.6 (CH5), AMP16.1 (VOUTA), FDB61.1
/LED 4x2 Right 4/ LDRow_Amps/Amp_OP_6: AD8.5 (CH4), AMP16.7 (VOUTB), FDB62.1
/LED 4x2 Right 4/ LDRow_Amps/Amp_OP_7: AD8.4 (CH3), AMP16.8 (VOUTC), FDB63.1
/LED 4x2 Right 4/ LDRow_Amps/Amp_OP_8: AD8.3 (CH2), AMP16.14 (VOUTD), FDB64.1
/LED 4x2 Right 4/ADC_SHDN: AD8.10 (SHDN/~CS), DMX1.9 (~Y6)
/LED 4x2 Right 4/LD1_B: DRV8.13 (LED7), LD57.3 (B)
/LED 4x2 Right 4/LD1_G: DRV8.12 (LED6), LD57.4 (G)
/LED 4x2 Right 4/LD1_R: LD57.1 (R), SR57.1 (+Ctr), SR57.4 (Load)
/LED 4x2 Right 4/LD2_B: DRV8.11 (LED5), LD58.3 (B)
/LED 4x2 Right 4/LD2_G: DRV8.10 (LED4), LD58.4 (G)
/LED 4x2 Right 4/LD2_R: LD58.1 (R), SR58.1 (+Ctr), SR58.4 (Load)
/LED 4x2 Right 4/LD3_B: DRV8.9 (LED3), LD59.3 (B)
/LED 4x2 Right 4/LD3_G: DRV8.8 (LED2), LD59.4 (G)
/LED 4x2 Right 4/LD3_R: LD59.1 (R), SR59.1 (+Ctr), SR59.4 (Load)
/LED 4x2 Right 4/LD4_B: DRV8.7 (LED1), LD60.3 (B)
/LED 4x2 Right 4/LD4_G: DRV8.6 (LED0), LD60.4 (G)
/LED 4x2 Right 4/LD4_R: LD60.1 (R), SR60.1 (+Ctr), SR60.4 (Load)
/LED 4x2 Right 4/LD5_B: DRV8.26 (LED16), LD61.3 (B)
/LED 4x2 Right 4/LD5_G: DRV8.27 (LED17), LD61.4 (G)
/LED 4x2 Right 4/LD5_R: LD61.1 (R), SR61.1 (+Ctr), SR61.4 (Load)
/LED 4x2 Right 4/LD6_B: DRV8.28 (LED18), LD62.3 (B)
/LED 4x2 Right 4/LD6_G: DRV8.29 (LED19), LD62.4 (G)
/LED 4x2 Right 4/LD6_R: LD62.1 (R), SR62.1 (+Ctr), SR62.4 (Load)
/LED 4x2 Right 4/LD7_B: DRV8.30 (LED20), LD63.3 (B)
/LED 4x2 Right 4/LD7_G: DRV8.31 (LED21), LD63.4 (G)
/LED 4x2 Right 4/LD7_R: LD63.1 (R), SR63.1 (+Ctr), SR63.4 (Load)
/LED 4x2 Right 4/LD8_B: DRV8.32 (LED22), LD64.3 (B)
/LED 4x2 Right 4/LD8_G: DRV8.33 (LED23), LD64.4 (G)
/LED 4x2 Right 4/LD8_R: LD64.1 (R), SR64.1 (+Ctr), SR64.4 (Load)
/LED 4x2 Right 4/SR1_R: DRV8.15 (LED8), SR57.2 (-Ctr)
/LED 4x2 Right 4/SR2_R: DRV8.16 (LED9), SR58.2 (-Ctr)
/LED 4x2 Right 4/SR3_R: DRV8.17 (LED10), SR59.2 (-Ctr)
/LED 4x2 Right 4/SR4_R: DRV8.19 (LED11), SR60.2 (-Ctr)
/LED 4x2 Right 4/SR5_R: DRV8.24 (LED15), SR61.2 (-Ctr)
/LED 4x2 Right 4/SR6_R: DRV8.23 (LED14), SR62.2 (-Ctr)
/LED 4x2 Right 4/SR7_R: DRV8.22 (LED13), SR63.2 (-Ctr)
/LED 4x2 Right 4/SR8_R: DRV8.20 (LED12), SR64.2 (-Ctr)
GND: AD1.9 (DGND), AD1.14 (AGND), AD2.9 (DGND), AD2.14 (AGND), AD3.9 (DGND), AD3.14 (AGND), AD4.9 (DGND), AD4.14 (AGND), AD5.9 (DGND), AD5.14 (AGND), AD6.9 (DGND), AD6.14 (AGND), AD7.9 (DGND), AD7.14 (AGND), AD8.9 (DGND), AD8.14 (AGND), ADSEL1.2, ADSEL2.2, ADSEL4.2, ADSEL5.2, DMX1.4 (~E1), DMX1.5 (~E2), DMX1.8 (GND), DRV1.4 (AD2), DRV1.5 (~OE), DRV1.14 (VSS), DRV1.18 (VSS), DRV1.21 (VSS), DRV1.25 (VSS), DRV1.34 (VSS), DRV1.39 (EXP), DRV2.4 (AD2), DRV2.5 (~OE), DRV2.14 (VSS), DRV2.18 (VSS), DRV2.21 (VSS), DRV2.25 (VSS), DRV2.34 (VSS), DRV2.39 (EXP), DRV3.4 (AD2), DRV3.5 (~OE), DRV3.14 (VSS), DRV3.18 (VSS), DRV3.21 (VSS), DRV3.25 (VSS), DRV3.34 (VSS), DRV3.39 (EXP), DRV4.2 (AD0), DRV4.4 (AD2), DRV4.5 (~OE), DRV4.14 (VSS), DRV4.18 (VSS), DRV4.21 (VSS), DRV4.25 (VSS), DRV4.34 (VSS), DRV4.39 (EXP), DRV5.4 (AD2), DRV5.5 (~OE), DRV5.14 (VSS), DRV5.18 (VSS), DRV5.21 (VSS), DRV5.25 (VSS), DRV5.34 (VSS), DRV5.39 (EXP), DRV6.4 (AD2), DRV6.5 (~OE), DRV6.14 (VSS), DRV6.18 (VSS), DRV6.21 (VSS), DRV6.25 (VSS), DRV6.34 (VSS), DRV6.39 (EXP), DRV7.4 (AD2), DRV7.5 (~OE), DRV7.14 (VSS), DRV7.18 (VSS), DRV7.21 (VSS), DRV7.25 (VSS), DRV7.34 (VSS), DRV7.39 (EXP), DRV8.4 (AD2), DRV8.5 (~OE), DRV8.14 (VSS), DRV8.18 (VSS), DRV8.21 (VSS), DRV8.25 (VSS), DRV8.34 (VSS), DRV8.39 (EXP), ISEL1.1, ISEL2.1, ISEL3.1, ISEL4.1, ISEL5.1, ISEL6.1, ISEL7.1, ISEL8.1, PH1.1, PH1.2, PH1.3, PH1.4, PH1.5, PH1.6, SFTR1.1 (GND)
I2C_SCL: DRV1.36 (SCL), DRV2.36 (SCL), DRV3.36 (SCL), DRV4.36 (SCL), DRV5.36 (SCL), DRV6.36 (SCL), DRV7.36 (SCL), DRV8.36 (SCL), PH1.27, PH1.28
I2C_SDA_3V3: PH1.29, PH1.30, SFTR1.3 (A1)
I2C_SDA_5V: DRV1.37 (SDA), DRV2.37 (SDA), DRV3.37 (SDA), DRV4.37 (SDA), DRV5.37 (SDA), DRV6.37 (SDA), DRV7.37 (SDA), DRV8.37 (SDA), PH1.31, PH1.32, SFTR1.6 (B1)
unnamed: DRV1.1 (REXT), ISEL1.2
unnamed: DRV1.35 (~RESET), PU1.2
unnamed: DRV2.1 (REXT), ISEL2.2
unnamed: DRV2.35 (~RESET), PU2.2
unnamed: DRV3.1 (REXT), ISEL3.2
unnamed: DRV3.35 (~RESET), PU3.2
unnamed: DRV4.1 (REXT), ISEL4.2
unnamed: DRV4.35 (~RESET), PU4.2
unnamed: DRV5.1 (REXT), ISEL5.2
unnamed: DRV5.35 (~RESET), PU5.2
unnamed: DRV6.1 (REXT), ISEL6.2
unnamed: DRV6.35 (~RESET), PU6.2
unnamed: DRV7.1 (REXT), ISEL7.2
unnamed: DRV7.35 (~RESET), PU7.2
unnamed: DRV8.1 (REXT), ISEL8.2
unnamed: DRV8.35 (~RESET), PU8.2
RB Voltage: AMP1.3 (VINA+), AMP1.5 (VINB+), AMP1.10 (VINC+), AMP1.12 (VIND+), AMP2.3 (VINA+), AMP2.5 (VINB+), AMP2.10 (VINC+), AMP2.12 (VIND+), AMP3.3 (VINA+), AMP3.5 (VINB+), AMP3.10 (VINC+), AMP3.12 (VIND+), AMP4.3 (VINA+), AMP4.5 (VINB+), AMP4.10 (VINC+), AMP4.12 (VIND+), AMP5.3 (VINA+), AMP5.5 (VINB+), AMP5.10 (VINC+), AMP5.12 (VIND+), AMP6.3 (VINA+), AMP6.5 (VINB+), AMP6.10 (VINC+), AMP6.12 (VIND+), AMP7.3 (VINA+), AMP7.5 (VINB+), AMP7.10 (VINC+), AMP7.12 (VIND+), AMP8.3 (VINA+), AMP8.5 (VINB+), AMP8.10 (VINC+), AMP8.12 (VIND+), AMP9.3 (VINA+), AMP9.5 (VINB+), AMP9.10 (VINC+), AMP9.12 (VIND+), AMP10.3 (VINA+), AMP10.5 (VINB+), AMP10.10 (VINC+), AMP10.12 (VIND+), AMP11.3 (VINA+), AMP11.5 (VINB+), AMP11.10 (VINC+), AMP11.12 (VIND+), AMP12.3 (VINA+), AMP12.5 (VINB+), AMP12.10 (VINC+), AMP12.12 (VIND+), AMP13.3 (VINA+), AMP13.5 (VINB+), AMP13.10 (VINC+), AMP13.12 (VIND+), AMP14.3 (VINA+), AMP14.5 (VINB+), AMP14.10 (VINC+), AMP14.12 (VIND+), AMP15.3 (VINA+), AMP15.5 (VINB+), AMP15.10 (VINC+), AMP15.12 (VIND+), AMP16.3 (VINA+), AMP16.5 (VINB+), AMP16.10 (VINC+), AMP16.12 (VIND+), RBSEL1.2
SPI_MISO_3V3: PH1.23, PH1.24, SFTR1.4 (A2)
SPI_MISO_5V: AD1.12 (DOUT), AD2.12 (DOUT), AD3.12 (DOUT), AD4.12 (DOUT), AD5.12 (DOUT), AD6.12 (DOUT), AD7.12 (DOUT), AD8.12 (DOUT), PH1.25, PH1.26, SFTR1.5 (B2)
SPI_MOSI: AD1.11 (DIN), AD2.11 (DIN), AD3.11 (DIN), AD4.11 (DIN), AD5.11 (DIN), AD6.11 (DIN), AD7.11 (DIN), AD8.11 (DIN), PH1.21, PH1.22
SPI_SCK: AD1.13 (CLK), AD2.13 (CLK), AD3.13 (CLK), AD4.13 (CLK), AD5.13 (CLK), AD6.13 (CLK), AD7.13 (CLK), AD8.13 (CLK), PH1.19, PH1.20
SPI_SS_0: DMX1.1 (A0), PH1.17, PH1.18
SPI_SS_1: DMX1.2 (A1), PH1.15, PH1.16
SPI_SS_2: DMX1.3 (A2), PH1.13, PH1.14
